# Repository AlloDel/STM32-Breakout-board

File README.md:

# STM32-breakout-board
A simple programmable board based on an stm32 f4 board

PDF and images of schematics added to the /docs directory

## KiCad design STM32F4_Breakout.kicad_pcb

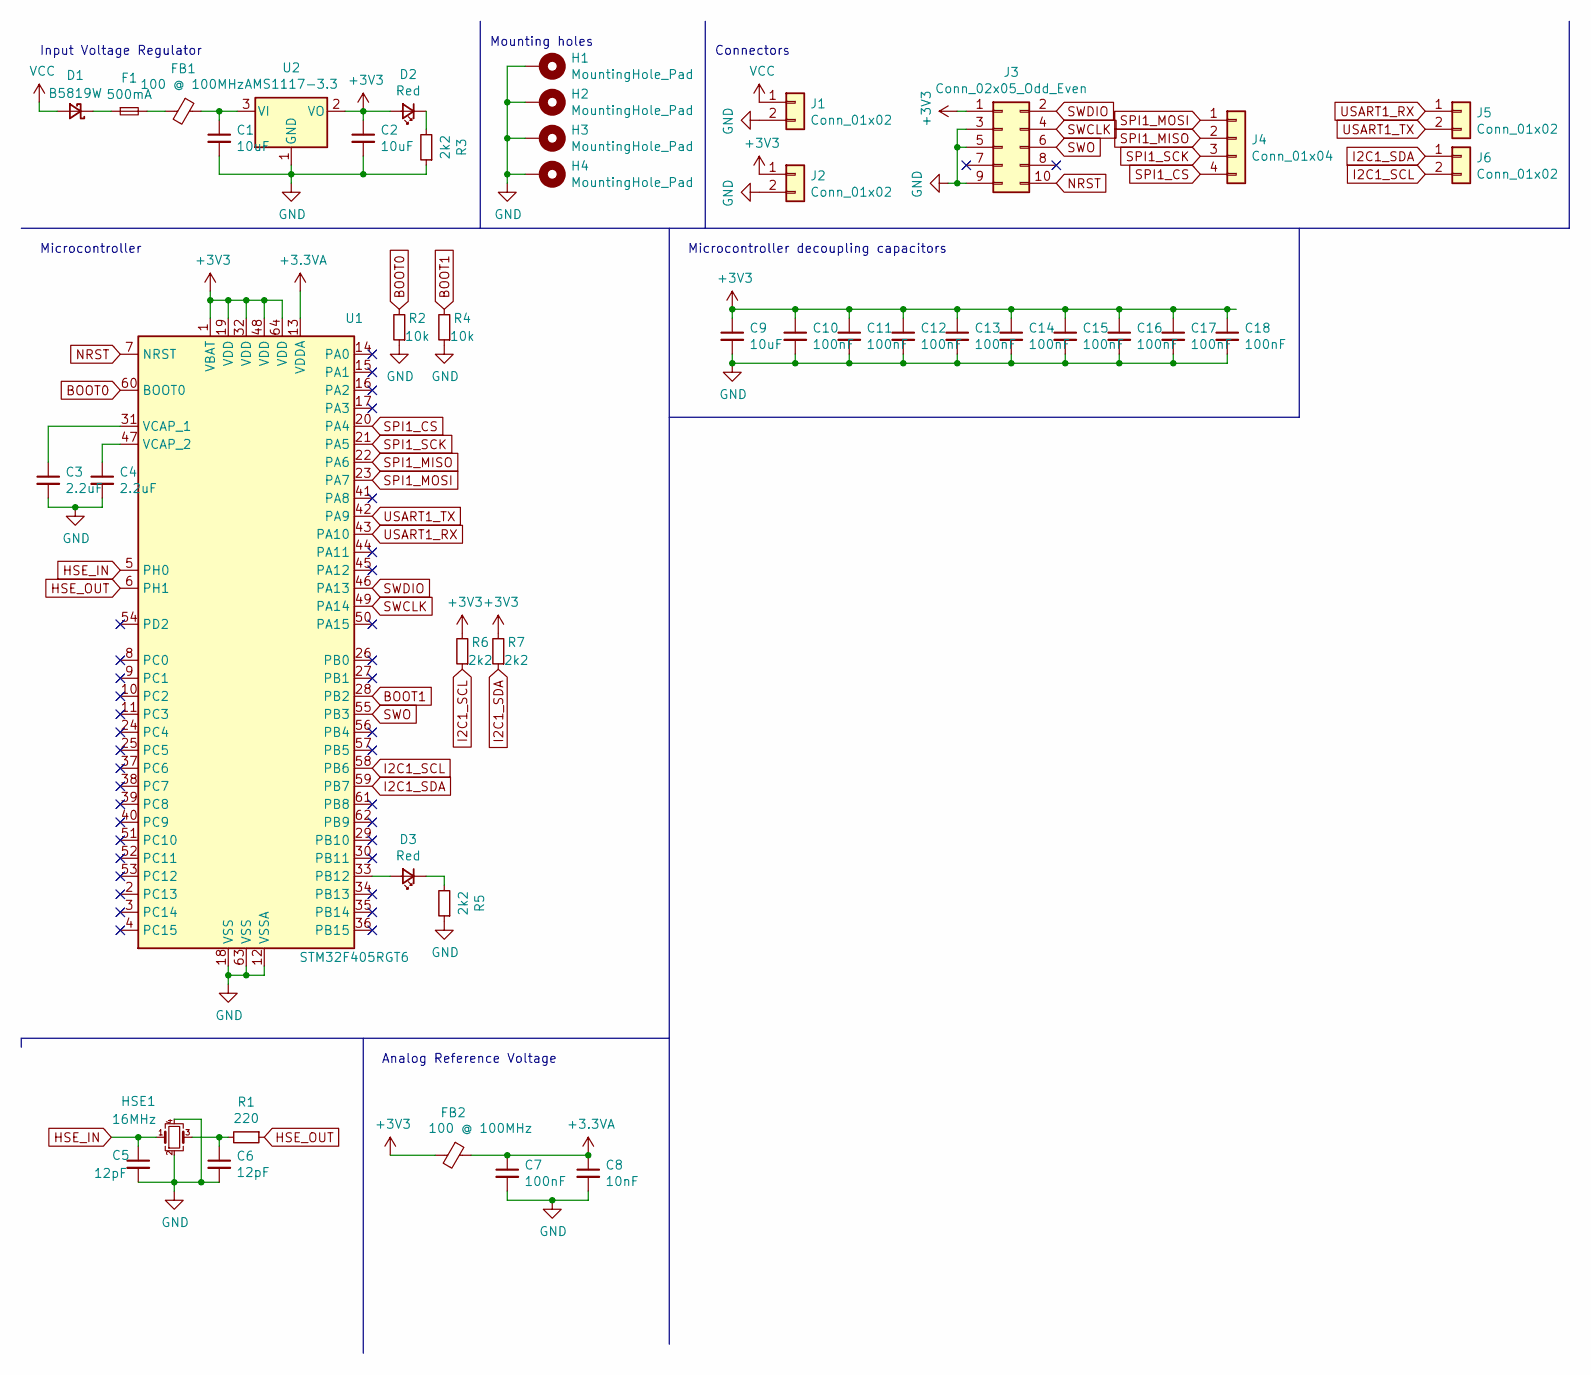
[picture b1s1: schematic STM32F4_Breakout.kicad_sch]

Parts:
C1, C2, C9: 10uF; C_0805_2012Metric
C3, C4: 2.2uF; C_0603_1608Metric
C5, C6: 12pF; C_0402_1005Metric
C7, C10, C11, C12, C13, C14, C15, C16, C17, C18: 100nF; C_0402_1005Metric
C8: 10nF; C_0402_1005Metric
D1: B5819W; D_SOD-123
D2, D3: Red; LED_0603_1608Metric
F1: 500mA; Fuse_0603_1608Metric
FB1, FB2: 100 @ 100MHz; L_0805_2012Metric
H1, H2, H3, H4: MountingHole_Pad; MountingHole_4.3mm_M4_Pad_Via
HSE1: 16MHz; Crystal_SMD_3225-4Pin_3.2x2.5mm
J1, J2, J5, J6: Conn_01x02; PinHeader_1x02_P2.54mm_Vertical
J3: Conn_02x05_Odd_Even; PinHeader_2x05_P1.27mm_Vertical_SMD
J4: Conn_01x04; PinHeader_1x04_P2.54mm_Vertical
R1: 220; R_0402_1005Metric
R2, R4: 10k; R_0402_1005Metric
R3, R5: 2k2; R_0603_1608Metric
R6, R7: 2k2; R_0402_1005Metric
U1: STM32F405RGT6; LQFP-64_10x10mm_P0.5mm
U2: AMS1117-3.3; SOT-223-3_TabPin2

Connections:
+3.3VA: C7.1, C8.1, FB2.1, U1.13 (VDDA)
+3V3: C2.1, C9.1, C10.1, C11.1, C12.1, C13.1, C14.1, C15.1, C16.1, C17.1, C18.1, D2.2 (A), FB2.2, J2.1, J3.1, R6.2, R7.2, U1.1 (VBAT), U1.19 (VDD), U1.32 (VDD), U1.48 (VDD), U1.64 (VDD), U2.2 (VO)
BOOT0: R2.2, U1.60 (BOOT0)
BOOT1: R4.2, U1.28 (PB2)
GND: C1.2, C2.2, C3.2, C4.2, C5.2, C6.2, C7.2, C8.2, C9.2, C10.2, C11.2, C12.2, C13.2, C14.2, C15.2, C16.2, C17.2, C18.2, H1.1, H2.1, H3.1, H4.1, HSE1.2, HSE1.4, J1.2, J2.2, J3.3, J3.5, J3.9, R2.1, R3.1, R4.1, R5.1, U1.12 (VSSA), U1.18 (VSS), U1.63 (VSS), U2.1 (GND)
HSE_IN: C5.1, HSE1.1, U1.5 (PH0)
HSE_OUT: R1.1, U1.6 (PH1)
I2C1_SCL: J6.2, R6.1, U1.58 (PB6)
I2C1_SDA: J6.1, R7.1, U1.59 (PB7)
NRST: J3.10, U1.7 (NRST)
unnamed: C1.1, FB1.1, U2.3 (VI)
unnamed: C3.1, U1.31 (VCAP_1)
unnamed: C4.1, U1.47 (VCAP_2)
unnamed: C6.1, HSE1.3, R1.2
unnamed: D1.1 (K), F1.1
unnamed: D2.1 (K), R3.2
unnamed: D3.1 (K), R5.2
unnamed: D3.2 (A), U1.33 (PB12)
unnamed: F1.2, FB1.2
SPI1_CS: J4.4, U1.20 (PA4)
SPI1_MISO: J4.2, U1.22 (PA6)
SPI1_MOSI: J4.1, U1.23 (PA7)
SPI1_SCK: J4.3, U1.21 (PA5)
SWCLK: J3.4, U1.49 (PA14)
SWDIO: J3.2, U1.46 (PA13)
SWO: J3.6, U1.55 (PB3)
USART1_RX: J5.1, U1.43 (PA10)
USART1_TX: J5.2, U1.42 (PA9)
VCC: D1.2 (A), J1.1

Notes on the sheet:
Mounting holes
Microcontroller
Microcontroller decoupling capacitors
Analog Reference Voltage
Connectors
Input Voltage Regulator

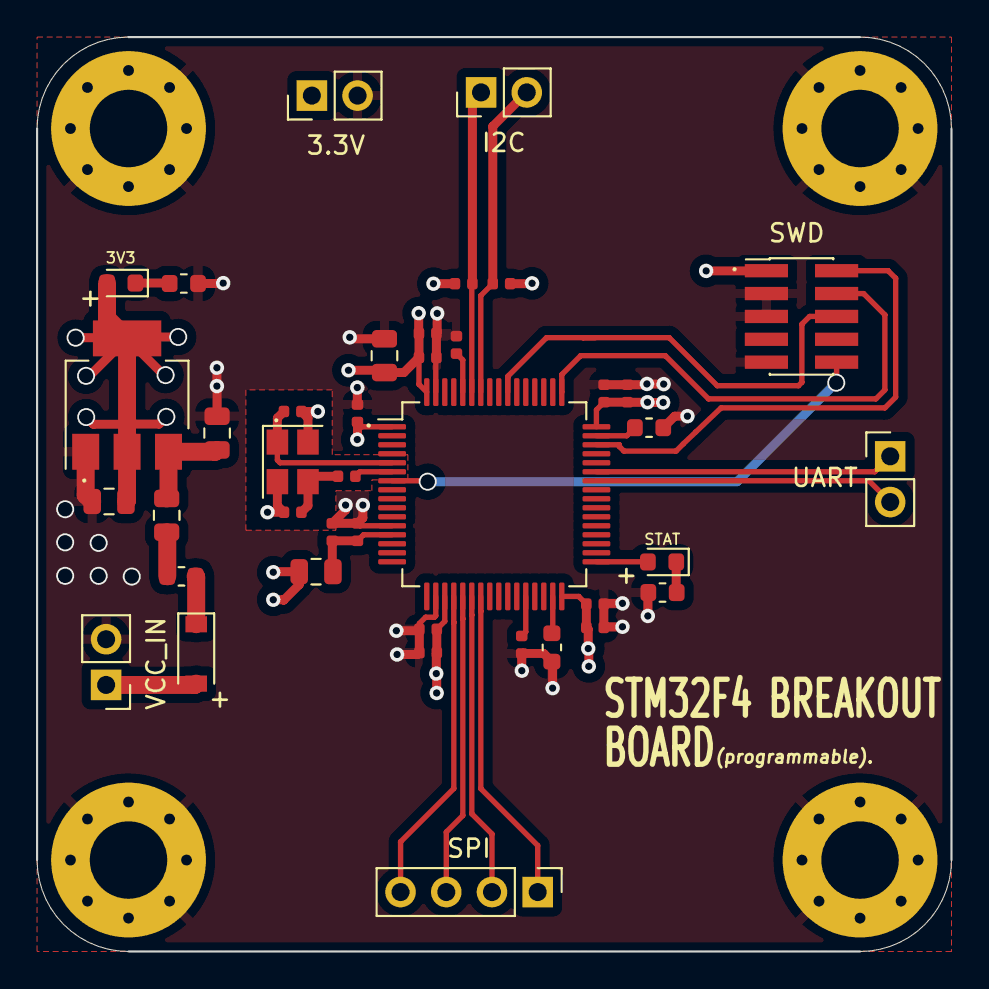
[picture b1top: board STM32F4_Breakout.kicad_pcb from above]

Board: 4 copper layers, 50.8 x 50.8 mm, 44 parts (0 on the bottom side), 29 nets.

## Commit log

2022-05-28 :star:initial commit
